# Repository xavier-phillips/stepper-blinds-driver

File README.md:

<div align="center">

# stepper-blinds-driver

**A NEMA 17 retrofit driver for beaded-chain roller blinds, designed to run under 40dB (noise not yet measured).**

Xavier Phillips

_The stepper blinds driver with the top lid removed, showing the main sprocket and the custom PCB._

</div>

---

## Contents
- [Overview](#overview)
- [Project Snapshot](#project-snapshot)
- [Technical Skills](#technical-skills)
- [Key Design Decisions](#key-design-decisions)
- [Hardware](#hardware)
- [Control Software](#control-software)
- [Build Log](#build-log)
- [Testing](#testing)
- [What's Next](#whats-next)
- [Reflection](#reflection)
- [Documentation](#documentation)

---

## Overview

### Problem
Opening blinds automatically has a range of benefits:
- Easier to wake up in mornings, and aligns circadian rhythm
- Provides more sunlight during day (for an office, this helps improve mood, among other health benefits)

Commercial options have some limitations:
- Can be very expensive
- Almost all commercial devices use geared DC motors, and are very loud when in operation (>50dB)

### Goal
1. Low-cost (<$100)
2. Compatible with beaded-chain blinds
3. Near-silent (<40dB)

### Features
1. Actuate beaded-chain with positional control (e.g. set to 50%)
   2. High precision is not crucial, aside from the start and end positions. However, end position is a mechanical limit (blinds cannot go further than highest position).
3. Controlled via Google Home or Home Assistant for scheduled automations.
4. Device should be compact
5. Powered externally with power supply (extremely clean, minimal, easy to hide cable)
6. Buttons should be minimised for aesthetic
   7. Possible structure
      1. Ver. 1 - up/down pushbuttons, power toggle. accessible port for microcontroller. no PCB (wires)
      2. Ver. 2 - power toggle only - small, hidden same-colour micro latch switch. hidden port for microcontroller (possibly a friction fit soft tpu plastic cover for it or similar, like a port cover, same colour). PCB.
8. Easily replaceable components (motor, PCB, microcontroller). highest priority for replicability is the cog/sprocket for the beaded chain which MUST be hot swappable in seconds
9. Custom PCB for final product
10. Clean, minimal box design with all internals hidden, mountable to a wall with standard screws

---

## Project Snapshot

### Details

| **Type**               | Personal project (no course/folio behind it)                     |
| ---------------------- | ---------------------------------------------------------------- |
| **Duration**           | Started ~30 June 2026, ongoing                                   |
| **Budget**             | $90.42 true project cost (target: <$100)                         |
| **Mechanism**          | Beaded-chain actuation, positional control (e.g. set to 50%)     |
| **MCU / Control**      | ESP32-C6 Mini Dev Board (Serial CLI Firmware v1.0)               |
| **Motor / driver**     | NEMA 17 Stepper Motor (34mm, 1.5A) + TMC2209 V2.0 Stepper Driver |
| **PCB**                | Custom 2-layer PCB for all electrical components                 |
| **Mechanical CAD**     | Onshape                                                          |
| **Manufacturing**      | 3D printing                                                      |

### Specifications

| Spec                     | Value                                                                   |
| ------------------------ | ----------------------------------------------------------------------- |
| Required pulling force   | 1.8kg (bucket-tested - see build log)                                   |
| Noise target             | <40dB (commercial cheap models are >50dB)                               |
| Travel range             | Unlimited                                                               |
| Holding torque           | N/A, designed for counterbalanced or friction-balanced household blinds |
| Power supply             | 12V 3A 36W power supply                                                 |
| Ecosystem tested against | Google Home or Home Assistant (per scope - not yet tested)              |

---

## Technical Skills

| Area                   | Skills and tools                                                                                                                                                 |
| ---------------------- | ---------------------------------------------------------------------------------------------------------------------------------------------------------------- |
| Mechanical design      | Onshape CAD - hot-swappable cog/sprocket mount for the beaded chain, compact enclosure                                                                           |
| PCB design             | KiCad - custom two-layer PCB, manufactured by JLCPCB; the first prototype used off-the-shelf breakouts (TMC2209 driver module, MP1584EN buck converter) on a perfboard |
| Embedded programming   | C++ / Arduino on ESP32 (Non-blocking stepper driver integration)                                                                                                 |
| Smart home integration | Google Home or Home Assistant, for scheduled automations                                                                                                         |
| Manufacturing          | 3D printing                                                                                                                                                      |

---

## Key Design Decisions

| Decision                     | Options considered                                                                                                                                                                                | Reasoning                                                                                                  |
| ---------------------------- | ------------------------------------------------------------------------------------------------------------------------------------------------------------------------------------------------- | ---------------------------------------------------------------------------------------------------------- |
| Motor + driver               | Ranked 10 motor setups against the <40dB noise / <$100 cost constraints (full comparison below); shortlisted NEMA 17 + TMC2209, JGY-370 Worm Gear Motor, NEMA 17 (5:1 Planetary Geared) + TMC2209 | This motor is extremely well documented and has a low noise level when paired with the TMC2209 controller. |
| PCB / prototyping approach   | Off-the-shelf breakout modules (TMC2209 driver, MP1584EN buck converter) on a prototype board vs. a from-scratch custom PCB                                                                       | V1 is on protoboard for now; custom PCB for final product is goal #7                                       |
| Button / enclosure interface | Minimal-none. The device is intended to be controlled wirelessly in the final iteration. Prototypes are controlled via serial CLI.                                                                 | Buttons should be minimised for aesthetic (goal #5)                                                        |

<details>
<summary><strong>Full motor comparison</strong> (from motor research notes)</summary>

> The biggest constraints for the motor are the <40dB requirement and the cost (total cost <$100)

**What impacts motor noise?**
- DC Brushed Motors - Brush scratching
- Geared Motors - Vibrations and friction
- Magnetic hum & coil whine

Overall, the magnitude of these sounds is also proportional to the RPM of the motor, so a slower RPM motor is ideal (and has the additional advantage of making the change in light level more gradual)

| Rank | Motor Setup | Category | Torque (Nm) | Max RPM | RPM Notes | Self-Locking | Approx. Noise Level (dB) | Dimensions (mm) | Volume (cm³) |
|---|---|---|---|---|---|---|---|---|---|
| 1 | NEMA 17 (Standard 42mm) + TMC2209 | Stepper | 0.40 | 400 | Variable | No | 38 | 42.3 x 42.3 x 40.0 | 71.57 |
| 2 | JGY-370 Worm Gear Motor (12V) | Brushed DC | 1.00 | 40 | Gearbox Fixed | Yes | 42 | 76.8 x 32.0 x 25.2 | 61.93 |
| 3 | NEMA 17 (5:1 Planetary Geared) + TMC2209 | Stepper | 1.50 | 80 | Variable | No | 43 | 42.3 x 42.3 x 61.3 | 109.68 |
| 4 | 35BYJ46 Geared Stepper (12V) | Stepper | 0.30 | 30 | Variable | No | 38 | 35.0 x 35.0 x 17.2 | 21.07 |
| 5 | BGM4108 Gimbal Motor + SimpleFOC | BLDC | 0.20 | 400 | Variable | No | 32 | 46.0 x 46.0 x 24.0 | 50.78 |
| 6 | 12V 28BYJ-48 (Modified to Bipolar) | Stepper | 0.10 | 15 | Variable | No | 35 | 28.0 x 28.0 x 19.0 | 14.90 |
| 7 | 25GA-370 Gear Motor (12V) | Brushed DC | 0.50 | 60 | Gearbox Fixed | No | 45 | 25.0 x 25.0 x 52.0 | 32.50 |
| 8 | NEMA 14 + TMC2209 Driver | Stepper | 0.15 | 400 | Variable | No | 38 | 35.0 x 35.0 x 26.0 | 31.85 |
| 9 | N20 Micro Gearmotor (12V, 60 RPM) | Brushed DC | 0.25 | 60 | Gearbox Fixed | No | 45 | 26.0 x 12.0 x 10.0 | 3.12 |
| 10 | MG996R Continuous Rotation Servo | Servo | 0.90 | 100 | Variable | No | 50 | 40.7 x 19.7 x 42.9 | 34.40 |

**Shortlist**

*1. NEMA 17 + TMC2209* - This motor is extremely well documented and has a low noise level when paired with the TMC2209 controller.

*2. JGY-370 Worm Gear Motor* - This is a slightly louder, more powerful alternative to the NEMA, the second best option if the NEMA turns out to be underpowered in torque (0.40 Nm vs 1.00 Nm). Has an additional benefit of being self-locking. Slightly above the noise limit by 2dB which is an acceptable margin.

*3. NEMA 17 (5:1 Planetary Geared) + TMC2209* - Same motor as Option 1, but geared to increase torque and reduce max RPM. Similar noise level and torque to Option 2, but ranked lower due to increased complexity.

</details>

---

## Hardware

### Mechanical (Onshape)
The main mechanical component is the mount, featuring two compartments. A thick-walled compartment which is load-bearing and contains the NEMA17, in addition to a thin-walled circuit compartment. 

To connect the NEMA17 to the mount, there is a face plate, which also features guides for the beaded-chain to be routed through.

There's also a cosmetic lid which is friction-fit using two pins for alignment and security, hiding the internal circuit while being easy to remove.

The sprocket is parametrically designed based on the following formulas.

The box features hexagonal ventilation holes which balance structural integrity and FDM manufacturability with sufficient surface area for thermal convection to prevent overheating.

### Electronics (KiCad)
The electronics involved in this project are for controlling and powering the motor. The ESP32 is the brain, allowing programmed movement logic and eventually communication with Google Home and other smart home systems via Matter over WiFi. The TMC2209 acts as an interface between the ESP32 and the NEMA17, and via the StealthChop2 feature, it allows ultra-quiet motor movement. The MP1584EN is a simple buck converter to step down the 12V from the power supply to the 5V required for the ESP32. 

I decided to use a custom PCB because I wanted to make multiple of the device, and eventually open-source it, so I decided inserting components into a PCB would be much easier than wiring spaghetti and frustrating breadboarding. It also gave me a chance to upskill KiCAD and learn about circuit schematics, rule checkers, and the PCB development and manufacturing process.

**BOM**

| Component | Source | Pack Size (Bought) | Qty Required | Pack Cost (AUD) | True Project Cost (AUD) |
|---|:---:|:---:|:---:|:---:|:---:|
| ESP32-C6 Mini Dev Board | Amazon AU | 1 | 1 | $25.01 | $25.01 |
| 12V 3A 36W Power Supply | Amazon AU | 1 | 1 | $21.99 | $21.99 |
| NEMA 17 Stepper Motor (34mm, 1.5A) | Amazon AU | 1 | 1 | $20.99 | $20.99 |
| TMC2209 V2.0 Stepper Driver | Amazon AU | 5 | 1 | $37.03 | $7.41 |
| MP1584EN 3A DC-DC Buck Converter | Amazon AU | 15 | 1 | $18.87 | $1.26 |
| Custom 2-Layer PCB | JLCPCB | 5 | 1 | $2.00 | $0.40 |
| M3 Button Head Screw Kit | Amazon AU | 300 | 8 | $10.99 | $0.29 |
| M3 Nylon Standoffs & Nuts Kit | Amazon AU | 320 | 4 | $12.99 | $0.16 |
| 3M VHB Double Sided Tape | Amazon AU | 33m | 10 cm | $12.99 | $0.04 |
| 2.1mmx5.5mm DC Power Jack (Panel Mount) | Amazon AU | 30 | 1 | $16.89 | $0.56 |
| 100µF 50V Electrolytic Capacitor (Polarized) | Jaycar Electronics | 1 | 1 | $1.00 | $1.00 |
| 60/40 Rosin Core Solder 0.71mm | Workshop | 15g | Variable | $0.00 | $0.00 |
| 24 AWG Solid Core Hookup Wire | Workshop | N/A | Variable | $0.00 | $0.00 |
| **Totals** | | | | **$180.75** | **$79.11** |

---

## Control Software
I wanted to keep this deliberately simple and write it fully myself so I could understand how the stepper control loop works, rather than relying on agentic tools to write something complex that I wouldn't fully understand under the hood.

**What it does:**
- Serial-based control to move to a pre-defined top and bottom position for the blinds
- Pause command to cancel movement with smooth acceleration.

**What it deliberately doesn't do (and why):**
- Other features (e.g. Matter over WiFi, auto calibration) have been left out due to time constraints for now and will be developed further in the future.

**Walkthrough**

* **`read_int()`:** Serial user input parser that checks for user commands and accepts valid inputs as commands (`0: Stop`, `1: Top`, `2: Bottom`).
* **`FastAccelStepper` Engine:** Asynchronously drives the STEP/DIR signal generation using ESP32 hardware timers, allowing smooth acceleration and deceleration ramps in the background.

---

# Build Log

### 2026-06-30 - Measuring required pull force

- Used a water bucket attached to the blinds to measure the force required to move them.
- At 1.7 kg, the blinds remained stationary. At 1.8 kg, the blinds were able to move.
- The 20 mm NEMA17 was determined to have insufficient torque, leading to the decision to use the 34 mm NEMA17 instead.

### 2026-07-02 - Initial CAD design

 - This design has a removable circuit box area, using dovetail cutouts. It also has removable guides for the beaded chains, secured by M2 screws.

### 2026-07-05 - Perfboard Assembly

 - Image of the components laid out on a perfboard. I've cut the perfboard down to a smaller size for compactness in this image, but for later perfboard iterations I used the full size, just for ease of wiring and troubleshooting (since it was only a prototype, the compactness was evaluated as somewhat irrelevant)

### 2026-07-07 - PCB Design 1

### 2026-07-10 - PCB Design 2

- Modified the PCB schematic in KiCAD to flip the footprint of the ESP32C6 by 180 degrees. This ensures that it can be wired correctly while having the USB port point towards the edge of the board, instead of the centre. Code was also updated to reflect the new pins.

### 2026-07-21 - Control Software Draft

```cpp
#include <Arduino.h>
#include <FastAccelStepper.h>

constexpr int PIN_EN = 14;
constexpr int PIN_SPREAD = 15;
constexpr int PIN_UART = 18;
constexpr int PIN_STEP = 20;
constexpr int PIN_DIR = 21;

constexpr int SPEED = 500;  // step per sec
constexpr int ACCEL = 1000; // step per sec^2

constexpr int TOP_POSITION = 0;       // steps
constexpr int BOTTOM_POSITION = 1000; // steps

enum user_input
{
  PAUSE,
  TOP,
  BOTTOM,
  OPTIONS_COUNT
};

user_input command = PAUSE;

int read_int()
{
  int command = -1;

  if (Serial.available() > 0)
  {
    command = Serial.parseInt();

    Serial.printf("Command received: %d\n", command);
  }

  return command;
};

FastAccelStepperEngine engine = FastAccelStepperEngine();
FastAccelStepper *stepper = nullptr;

void setup()
{
  pinMode(PIN_STEP, OUTPUT);
  digitalWrite(PIN_SPREAD, LOW);

  Serial.begin(115200);
  delay(1000);

  engine.init();

  stepper = engine.stepperConnectToPin(PIN_STEP);

  if (stepper)
  {
    Serial.println("SUCCESS: Stepper connected!");

    stepper->setDirectionPin(PIN_DIR);
    stepper->setEnablePin(PIN_EN);
    stepper->setAutoEnable(true);
    stepper->setSpeedInHz(SPEED);
    stepper->setAcceleration(ACCEL);
    stepper->setCurrentPosition(0);
  }
  else
  {
    Serial.println("ERROR: Stepper failed to connect.");
  }
}

void loop()
{

  command = static_cast<user_input>(read_int());

  if (command != -1)
  {
    Serial.printf("Current Position: %d Enter an option:\n\t0.Pause\n\t1. Move Top\n\t2. Move Bottom\n", stepper->getCurrentPosition());

    switch (command)
    {
    case PAUSE:
      Serial.println("Action: STOP");
      stepper->stopMove();
      break;

    case TOP:
      Serial.println("Action: TOP");
      stepper->moveTo(TOP_POSITION, false);
      break;

    case BOTTOM:
      Serial.println("Action: BOTTOM");
      stepper->moveTo(BOTTOM_POSITION, false);
      break;

    default:
      Serial.printf("Invalid command! Enter a valid integer between 1 and %d.\n", OPTIONS_COUNT);
      break;
    }
  }
}
```
 - Just a basic serial-control script for testing basic functionality (movement up, down, and pausing)

### 2026-07-24 - CAD Design 2

 - This was a major transition. The two-box dovetail architecture was replaced with a single box with two compartments. 

### 2026-07-30 - Motor Testing

- Upon arrival of the board (**2026-07-30**) and initial basic testing of roller blind movement (a short test program), I determined that the NEMA17 tended to stall quite easily. Upon closer inspection and troubleshooting (including verifying that it did work with a much lighter, smaller roller blind), I determined that the cause was simply insufficient current. The 12V wall adapter I was using only had a rated current of 1A, much less than the planned 3A.
- Order a 12V 3A power supply ASAP, in order to provide sufficient power for the NEMA17 to lift basic blinds.

---

## Testing

| Test                                 | Result          |
| ------------------------------------ | --------------- |
| Bucket test - required pulling force | 1.8kg confirmed |
| Noise level (<40dB target)           | Not yet tested  |

---

## What's Next

- The next step is writing the implementation that includes Matter, rather than the basic hard-coded values the script currently uses. 
	- For the implementation, I want to keep it buttonless for aesthetics and simplicity of circuitry. So I'm planning to use StallGuard to determine increased resistance at the top of the range of motion (ROM) for calibration, as well as a reduced resistance at the bottom of ROM.

---

## Reflection

I learned a massive amount from this project. On the CAD side, I learned about using variables in my designs, rather than "magic numbers" for dimensions, so everything in my design is fully adjustable via the variables table. I also learned about a lot more Onshape's sketch tools (tangent, normal, and perpendicular constraints), as well as their 3D tools (Featurescripts like Grid Extrude for ventilation, alongside operations like revolve which I used for the sprocket). 

I also learned KiCAD from scratch during this project, which was a great learning experience and upskilling opportunity into a new field. Historically I used graphical software like Canva or Illustrator for circuit diagrams, but learning how to write proper, verified schematics was really enjoyable, and seeing my own custom-designed PCB arrive was extremely rewarding. Contrary to what I used to assume about PCBs, it actually _saved_ me time, as I used to have to spend weeks fiddling with breadboards because I didn't take the time to plan my circuit thoroughly. That, combined with the time saved from soldering (only took ~10min to solder the entire PCB!), allowed me to finalise all electronics in about a week.

---

## Documentation

- Firmware Code: [`/firmware`](firmware/)
- PCB (Schematic + Gerbers): [`/hardware/pcb`](hardware/pcb/)
- CAD Files: [`/hardware/cad`](hardware/cad/)

## Acknowledgements & License

[gin66/FastAccelStepper: A high speed stepper library for Atmega 168/328p (nano), Atmega32u4, Atmega 2560, ESP32, ESP32S2, ESP32S3, ESP32C3, ESP32C6, Atmel SAM Due, Raspberry pi pico and pico 2](https://github.com/gin66/FastAccelStepper)

This project is licensed under the MIT License. See the [LICENSE](LICENSE) file for details.

<p align="center"><sub>Personal project, July 2026.</sub></p>

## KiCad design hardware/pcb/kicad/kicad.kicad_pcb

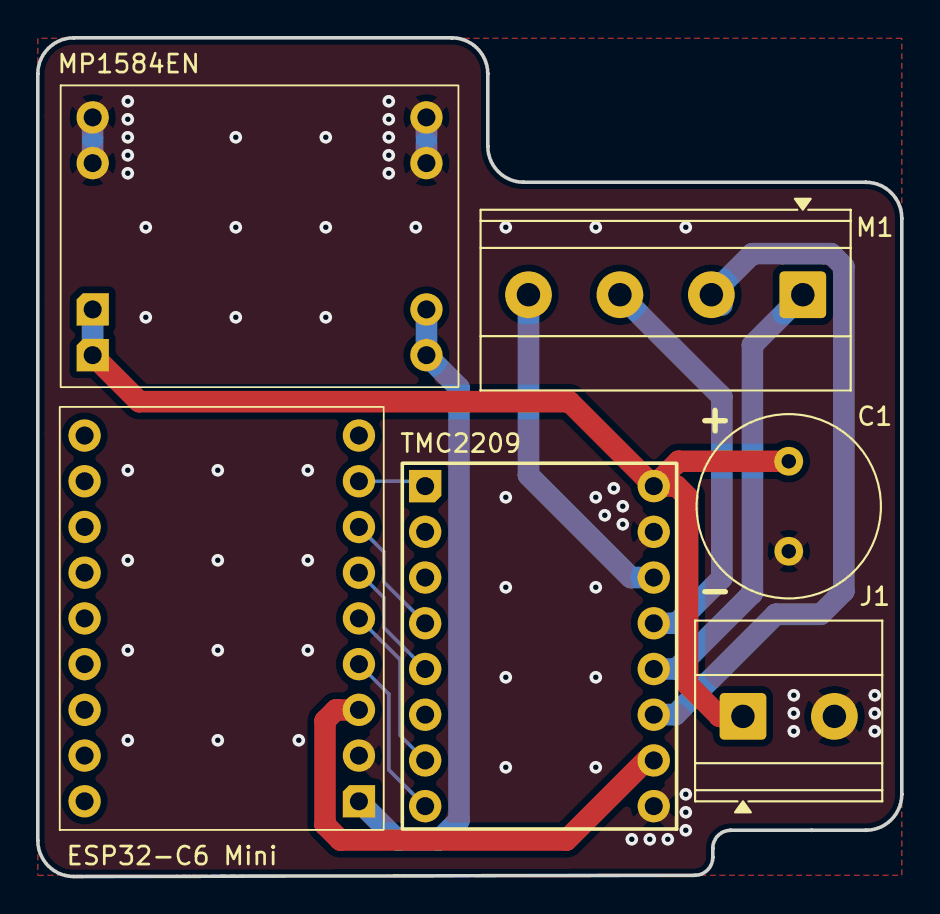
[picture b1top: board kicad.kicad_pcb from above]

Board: 2 copper layers, 48.0 x 46.6 mm, 6 parts (0 on the bottom side), 13 nets.

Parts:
C1: 100µF; C_Radial_D10.0mm_H20.0mm_P5.00mm
ESP32-C6-Super-Mini1: ESP32-C6-Super-Mini-Header
J1: Barrel_Jack; TerminalBlock_Phoenix_MKDS-1,5-2-5.08_1x02_P5.08mm_Horizont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
M1: Stepper_Motor_bipolar; TerminalBlock_Phoenix_MKDS-1,5-4-5.08_1x04_P5.08mm_Horizont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
MP1584EN1: MP1584EN-Module
TMC2209: TMC2209-Module

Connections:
+3.3V: ESP32-C6-Super-Mini1.3 (3V3), TMC2209.10 (VIO)
+5V: ESP32-C6-Super-Mini1.1 (5V), MP1584EN1.3 (OUT+)
+12V: C1.1, J1.1, MP1584EN1.1 (IN+), TMC2209.16 (VM)
/M1A: M1.1, TMC2209.12 (M1A)
/M1B: M1.2 (-_2), TMC2209.11 (M1B)
/M2A: M1.3, TMC2209.13 (M2A)
/M2B: M1.4, TMC2209.14 (M2B)
/MOT_DIAG: ESP32-C6-Super-Mini1.7 (GP3), TMC2209.4 (SPREAD)
/MOT_DIR: ESP32-C6-Super-Mini1.4 (GP0), TMC2209.8 (DIR)
/MOT_EN: ESP32-C6-Super-Mini1.8 (GP4), TMC2209.1 (EN)
/MOT_STEP: ESP32-C6-Super-Mini1.5 (GP1), TMC2209.7 (STEP)
/MOT_UART: ESP32-C6-Super-Mini1.6 (GP2), TMC2209.5 (PDN_UART1)
GND: C1.2, ESP32-C6-Super-Mini1.2 (GND), J1.2, MP1584EN1.2 (IN-), MP1584EN1.4 (OUT-), TMC2209.9 (GND), TMC2209.15 (GND)
